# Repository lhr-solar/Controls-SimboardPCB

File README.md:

# Controls-SimboardPCB

Board's Purpose:

The Controls Sim Board interfaces with the Controls Leader Board in order to simulate the interfacing of the controls system on the car. 

Connections:

LEDs:
* Motor main contactor signal (D1)
* Motor precharge contactor signal (D2)
* Array main contactor signal (D3)
* Array precharge contactor signal  (D4)
Potentiometers:
* Accelerator
* Brake
Switches:
* Ignition
Other:
* CAN connections
* Controls Minion Board passthrough

Mouser BOM:
* Cart link: https://www.mouser.com/ProjectManager/ProjectDetail.aspx?AccessID=63b65d6ddb
* (Spreadsheet of BOM in repo as "Controls-Simboard MouserBom.xls")

Components Outside of Regular Volume:
* 538-43045-1412 (7x2 Molex connector)
* 538-43650-0415 (4x1 Molex connector)
* 538-43045-0612 (3x2 Molex connector)
* 10WA325 (Rotary switch)
* 179-TS16121295260STT (Push button)
* 652-PA45432015CPA503 (Slide Potentiometer)

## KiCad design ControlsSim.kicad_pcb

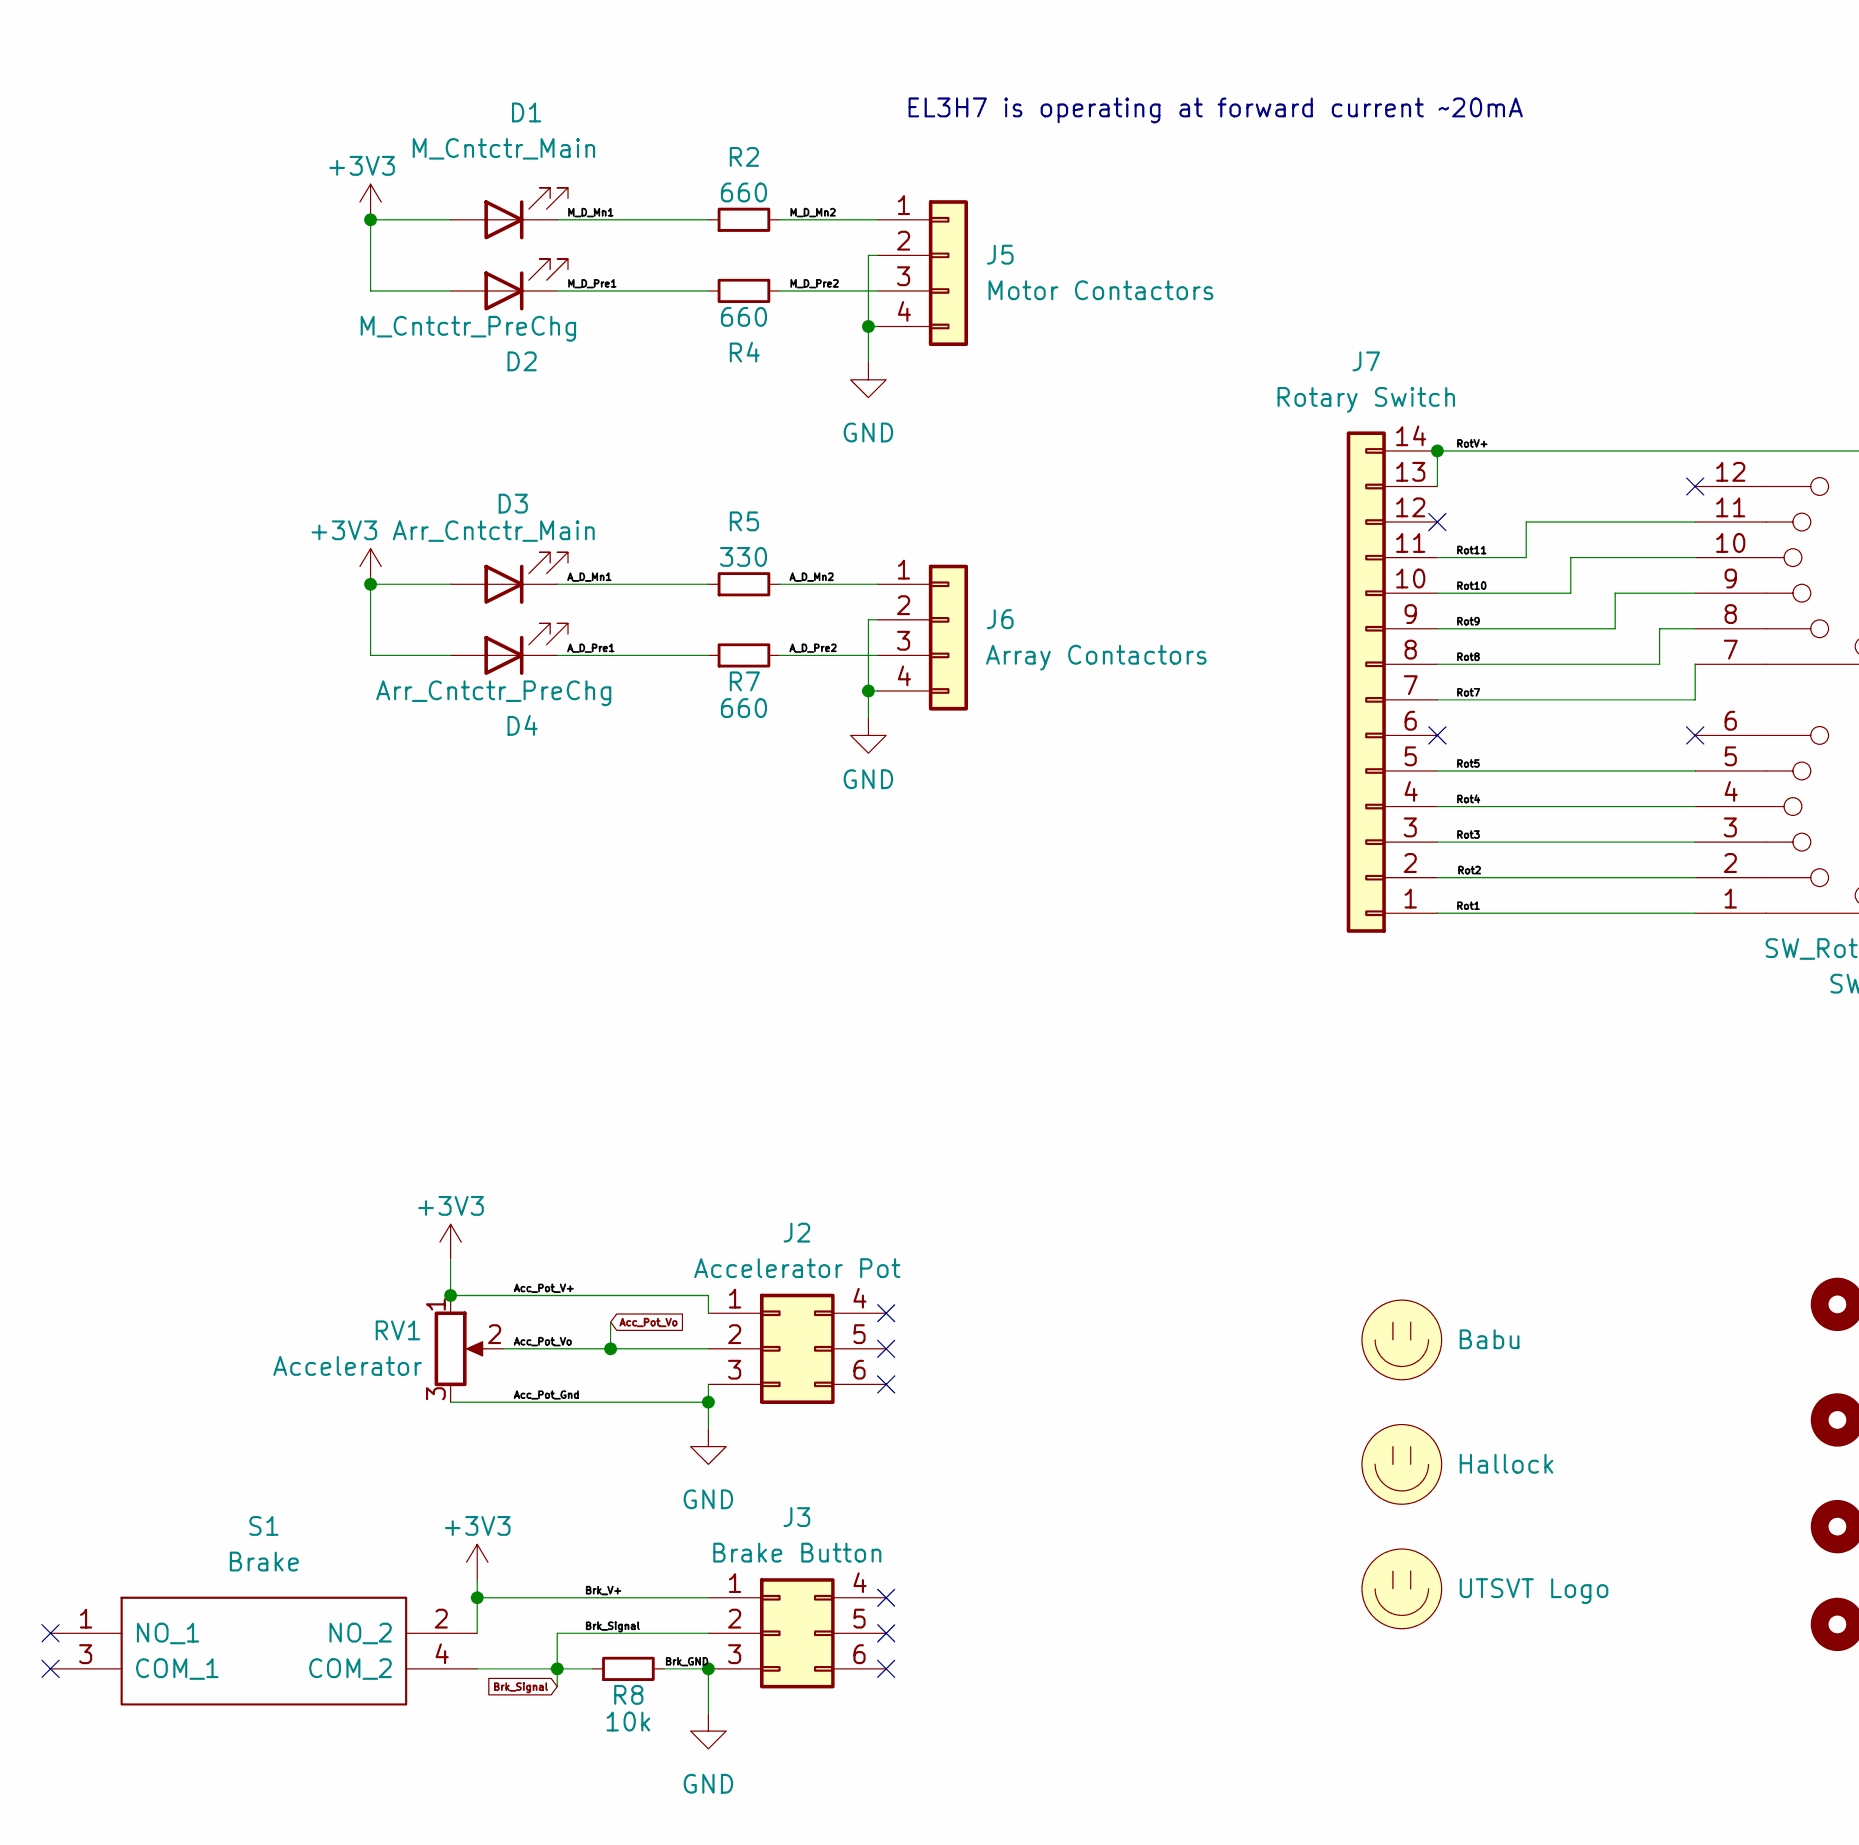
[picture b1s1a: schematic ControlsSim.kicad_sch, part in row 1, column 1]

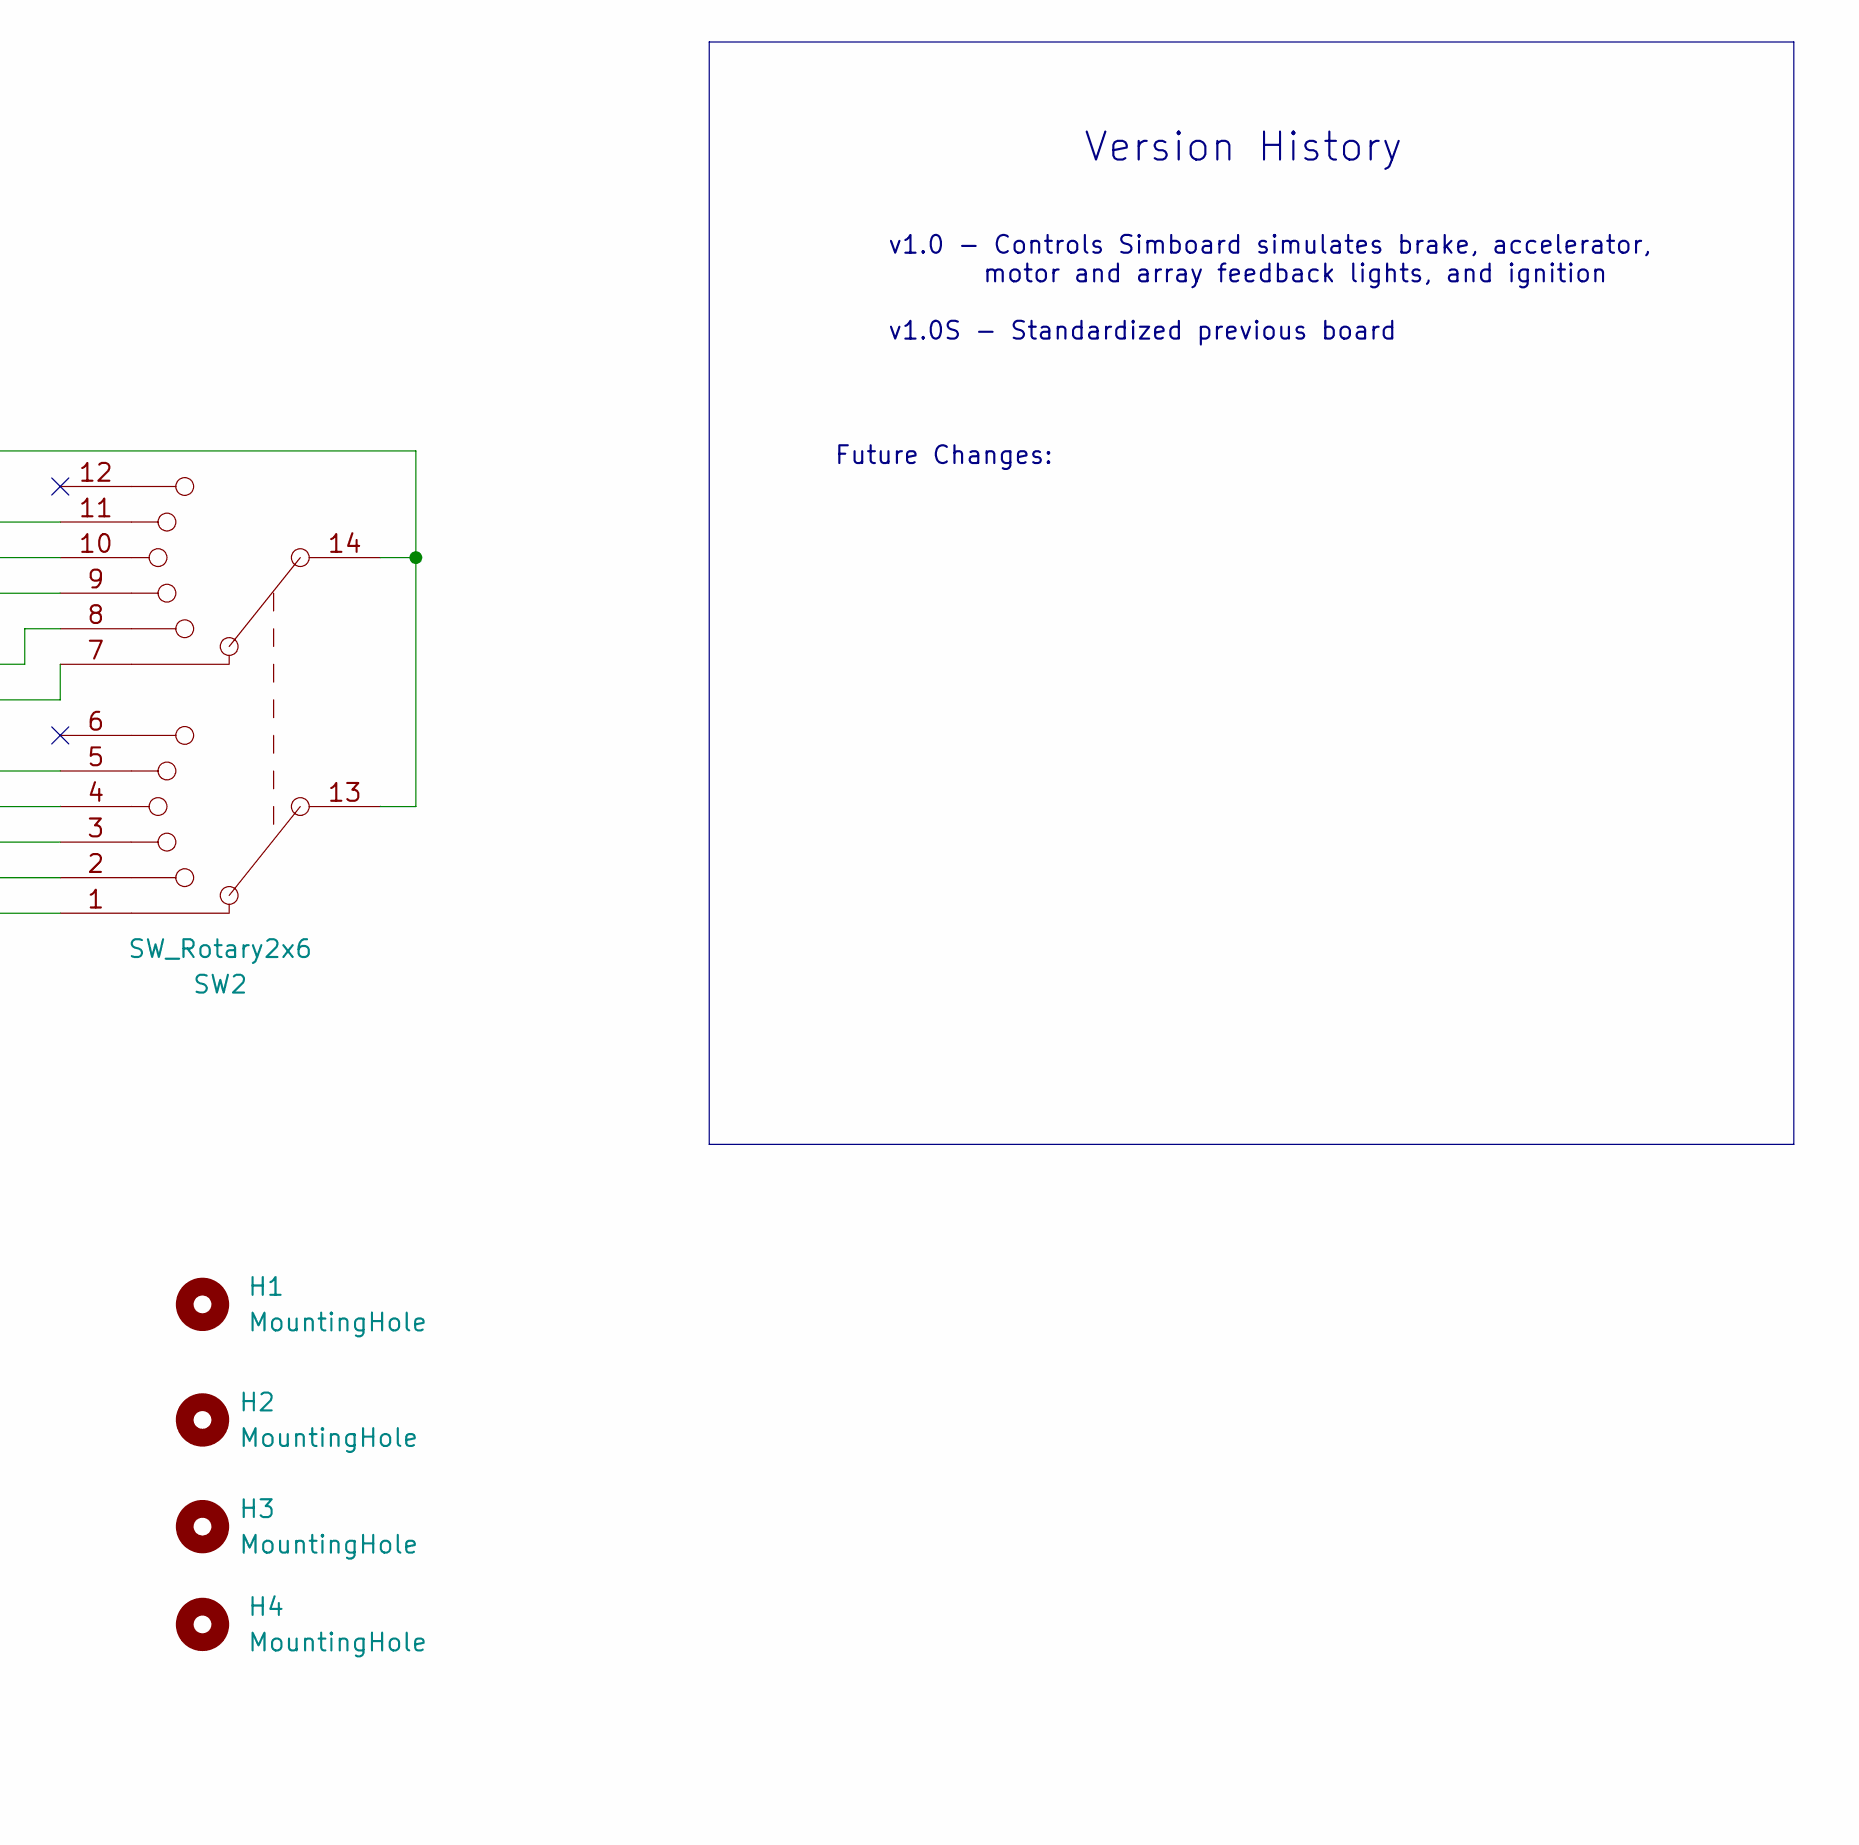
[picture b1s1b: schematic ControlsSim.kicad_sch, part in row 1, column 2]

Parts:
D1: M_Cntctr_Main; LED_0805_2012Metric; MFG PN APTD2012LSYCK
D2: M_Cntctr_PreChg; LED_0805_2012Metric; MFG PN APTD2012LSURCK
D3: Arr_Cntctr_Main; LED_0805_2012Metric; MFG PN APTD2012LVBC/D
D4: Arr_Cntctr_PreChg; LED_0805_2012Metric; MFG PN APTD2012LCGCK
H1, H2, H3, H4: MountingHole; MountingHole_3.2mm_M3
J2: Accelerator Pot; Molex_Micro-Fit_3.0_43045-0612_2x03_P3.00mm_Vertical
J3: Brake Button; Molex_Micro-Fit_3.0_43045-0612_2x03_P3.00mm_Vertical
J5: Motor Contactors; Molex_Micro-Fit_3.0_43650-0415_1x04_P3.00mm_Vertical
J6: Array Contactors; Molex_Micro-Fit_3.0_43650-0415_1x04_P3.00mm_Vertical
J7: Rotary Switch; Molex_Micro-Fit_3.0_43045-1412_2x07_P3.00mm_Vertical
LOGO1: Hallock; Hallock_Image_Small
LOGO2: UTSVT Logo; UTSVT_Logo_Symbol
LOGO3: Babu; Babu the Builder
R2, R4, R7: 660; R_0805_2012Metric
R5: 330; R_0805_2012Metric
R8: 10k; R_0805_2012Metric; Mfg PN CRCW080510K0FKEAC
RV1: Accelerator; PTA4543
S1: Brake; TS16121295BK260SMTTR; Manufacturer_Part_Number TS16-1212-95-BK-260-SMT-TR
SW2: SW_Rotary2x6; CK1035_resized

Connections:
+3V3: D1.2 (A), D2.2 (A), D3.2 (A), D4.2 (A), J2.1, J3.1, RV1.1, S1.2 (NO_2)
/A_D_Mn1: D3.1 (K), R5.1
/A_D_Mn2: J6.1, R5.2
/A_D_Pre1: D4.1 (K), R7.1
/A_D_Pre2: J6.3, R7.2
/M_D_Mn1: D1.1 (K), R2.1
/M_D_Mn2: J5.1, R2.2
/M_D_Pre1: D2.1 (K), R4.2
/M_D_Pre2: J5.3, R4.1
/Rot1: J7.1, SW2.1
/Rot2: J7.2, SW2.2
/Rot3: J7.3, SW2.3
/Rot4: J7.4, SW2.4
/Rot5: J7.5, SW2.5
/Rot7: J7.7, SW2.7
/Rot8: J7.8, SW2.8
/Rot9: J7.9, SW2.9
/Rot10: J7.10, SW2.10
/Rot11: J7.11, SW2.11
/RotV+: J7.13, J7.14, SW2.13, SW2.14
Acc_Pot_Vo: J2.2, RV1.2
Brk_Signal: J3.2, R8.1, S1.4 (COM_2)
GND: J2.3, J3.3, J5.2, J5.4, J6.2, J6.4, R8.2, RV1.3

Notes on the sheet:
v1.0 - Controls Simboard simulates brake, accelerator, motor and array feedback lights, and ignition v1.0S - Standardized previous board
Future Changes:
EL3H7 is operating at forward current ~20mA
Version History

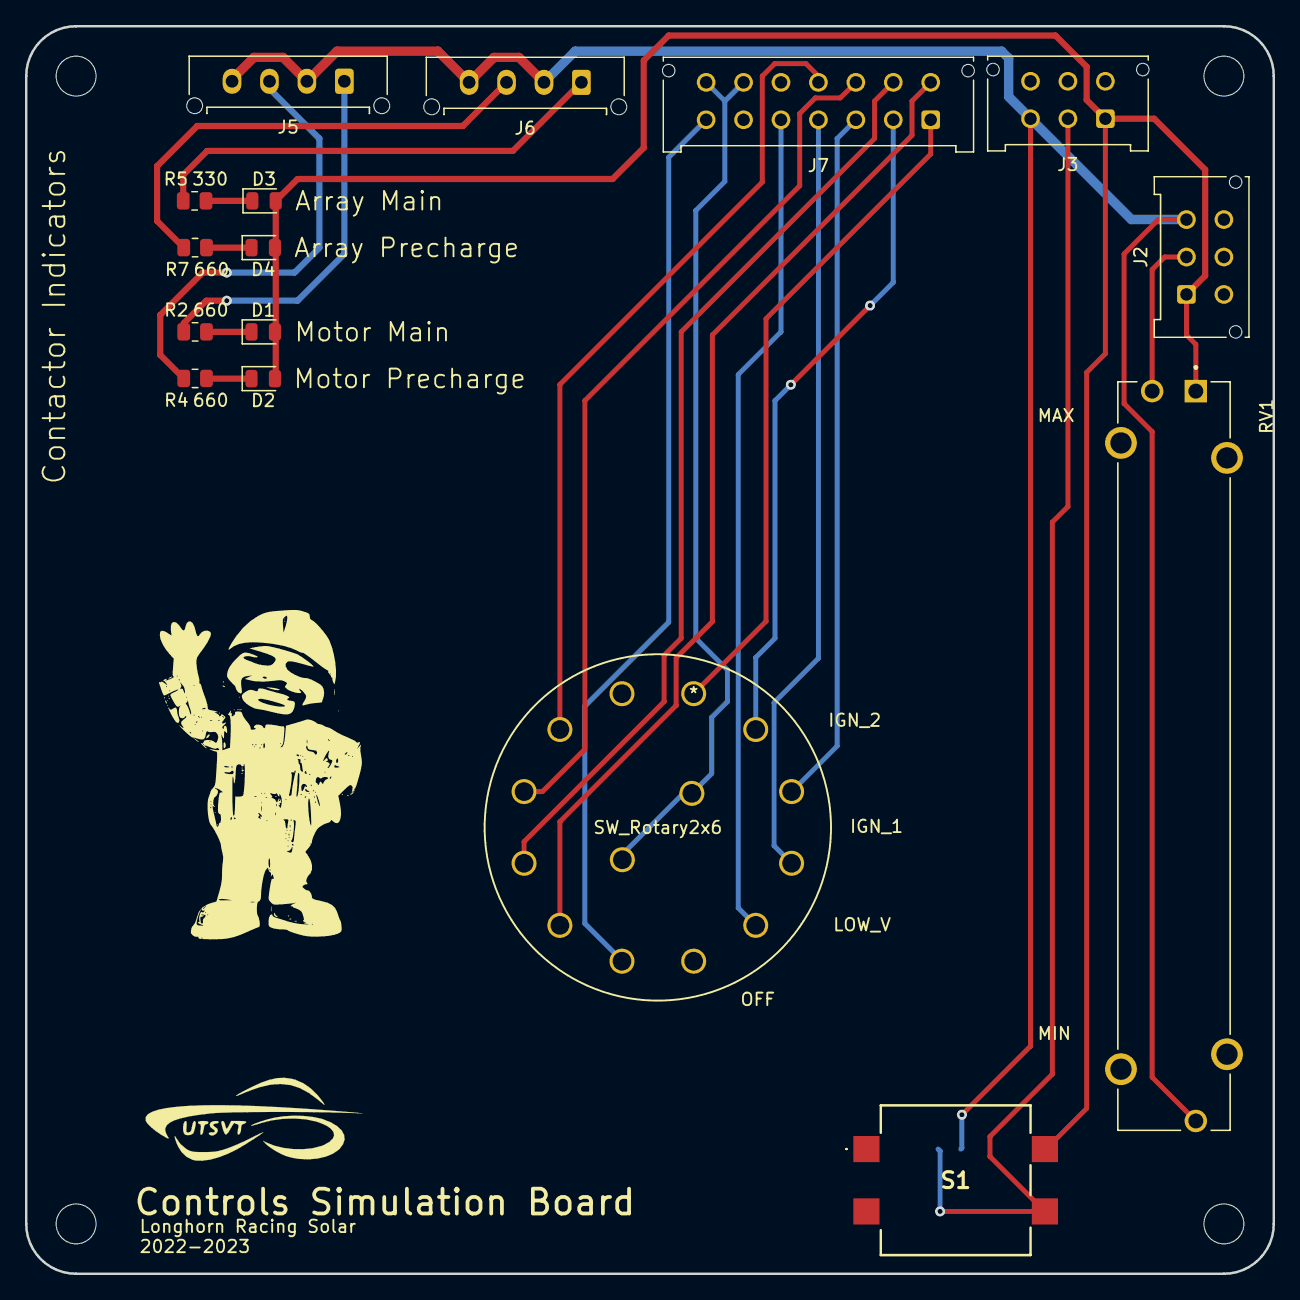
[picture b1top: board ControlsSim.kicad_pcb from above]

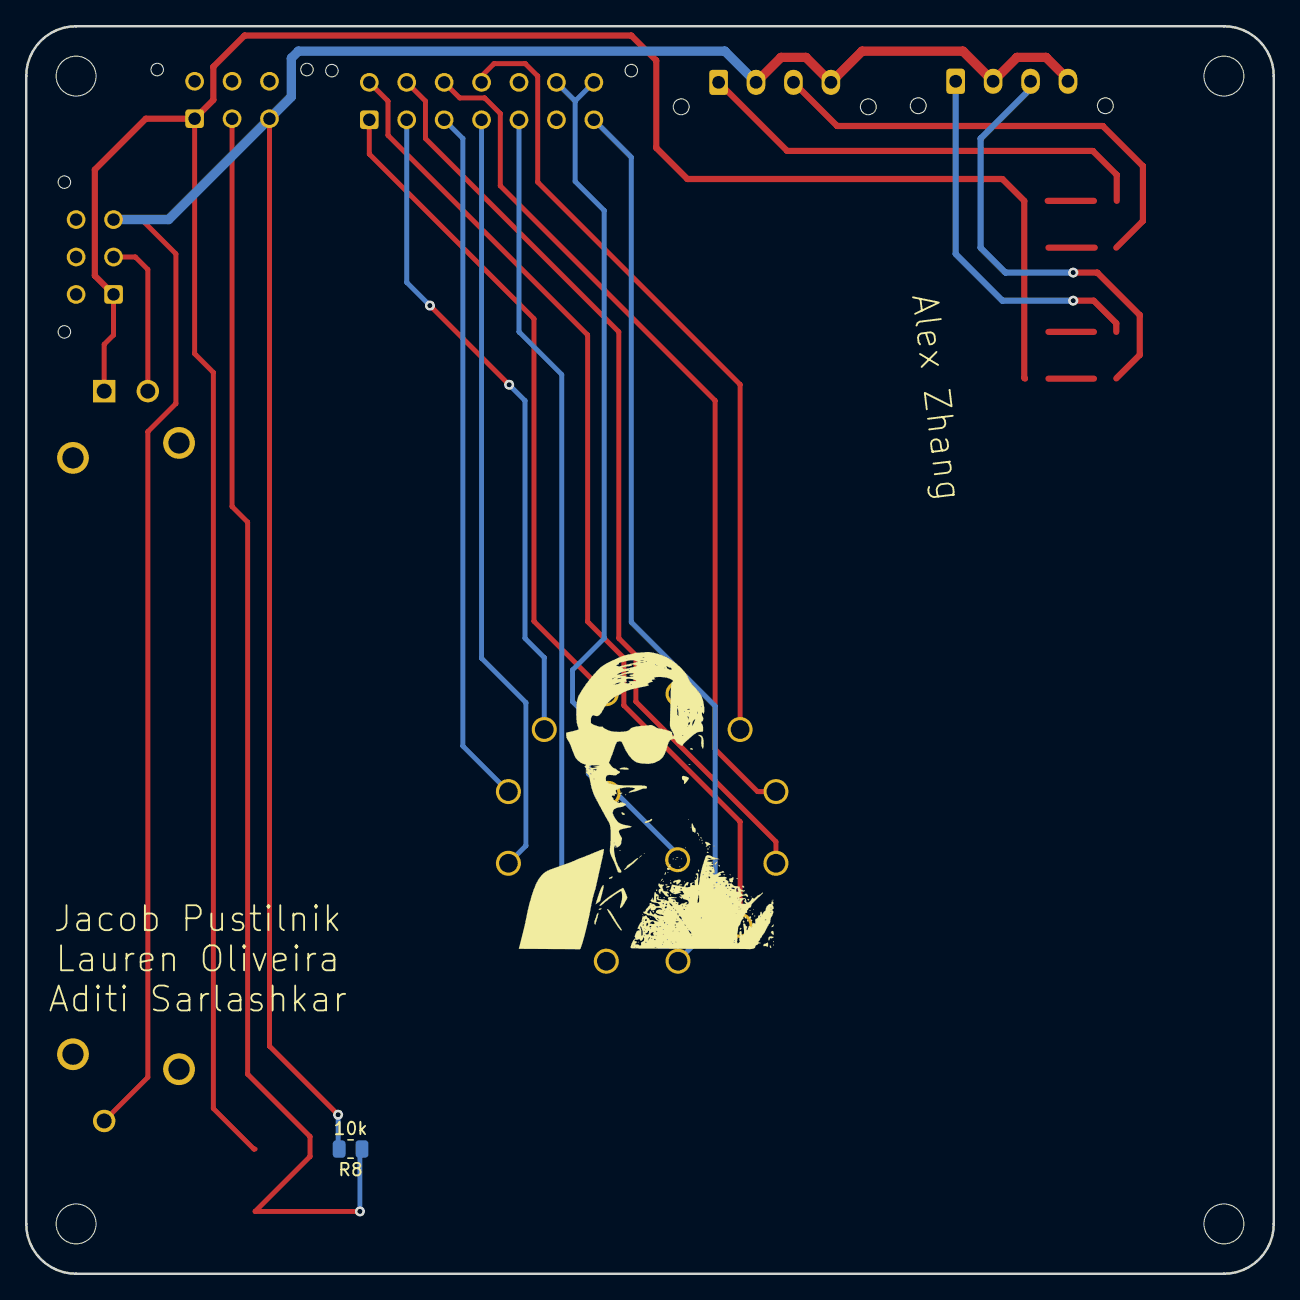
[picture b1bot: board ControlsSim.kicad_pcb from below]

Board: 2 copper layers, 100.0 x 100.0 mm, 24 parts (2 on the bottom side), 23 nets.

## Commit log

2022-09-24 Adds pcb parts library
2022-09-24 Empty KiCad file
2022-10-01 Blank KiCad file and branch creation
2022-10-15 Controls Simboard Block Diagram
2022-10-22 Initial schematic with parts
2022-10-29 Revised schematic with input from Babu, intial PCB layout
2022-11-12 almost final PCB
2022-11-12 added logos
2022-12-03 removed display connector
2022-12-03 minor silkscreen text movement
2022-12-03 shortened traces of contactor LEDs, moved upward
2023-01-12 Changed LED colors to use all four colors, one for each contactor
2023-02-04 Generated gerbers and drill files
2023-02-05 Added zip file of gerbers
2023-05-22 Beginning of Standardization
2023-05-22 Updated to correct git ignore
2023-05-22 Updated .gitignore again
2023-05-22 updated gitignore again again
2023-05-22 README and BOM Finished
    Updated the README according to new guidelines and added the BOM spreadsheet as a .xls
2023-05-25 Added Missing Datasheets
2023-05-25 Fixed DRC
2023-05-28 Fixed Submodule, added Version History, and fixed folder organization
2023-05-29 KiCad 7.0
2023-06-14 Updated version history and implemented a fix for 3dmodels to be applied next commit
2023-06-19 Fixed directories for footprints and 3D models, also fixed incorrect footprint and 3d model for rotary encoder.
2023-08-26 Fixed DRC issue and removed extraneous traces
2023-09-02 added schematic and PCB of first revision
2023-09-02 initial schematic and PCB and gerbers
2023-09-23 Updated silkscreen that Controls wanted
2023-09-23 Fixed resistor value and layout, fixed labels for rotary encoder.
2023-09-23 Updated ibom and gerbers
2023-09-23 fixed ibom
2023-09-30 Redesigned the layout to better accomodate the new rotary encoder footprint
2023-09-30 Fixed a few errors with the edge cuts (oopsies)
2023-09-30 Updated BOM

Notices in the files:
parts and their libraries:
Copyright 2016 Accelerated Designs. All rights reserved.
